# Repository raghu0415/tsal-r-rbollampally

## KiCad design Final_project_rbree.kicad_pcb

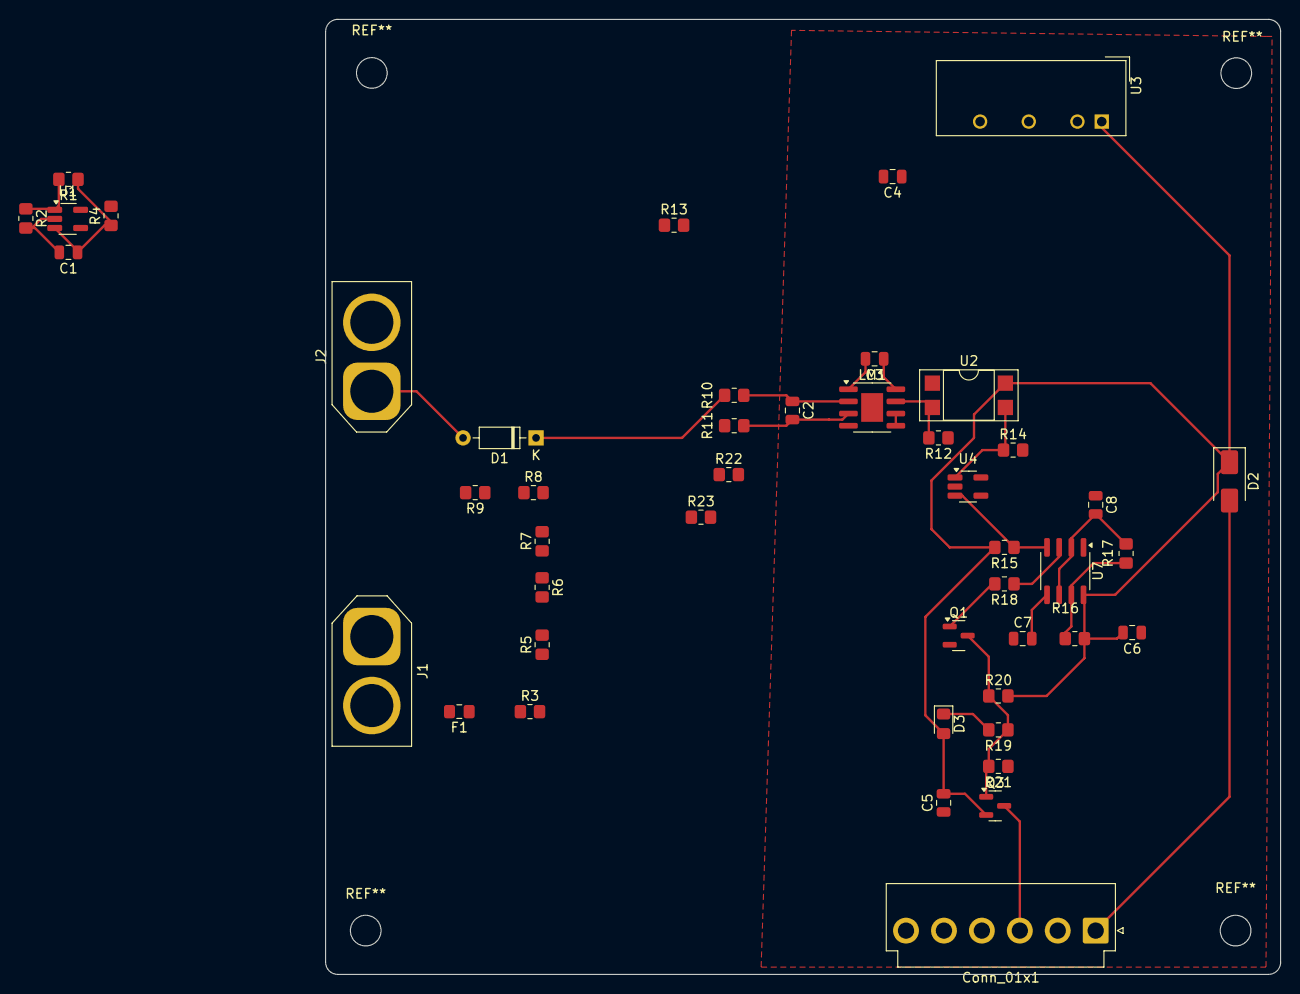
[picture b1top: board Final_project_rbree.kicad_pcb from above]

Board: 2 copper layers, 99.7 x 99.7 mm, 46 parts (0 on the bottom side), 29 nets.

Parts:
C1: 0.1uF; C_0805_2012Metric
C2: 10n; C_0805_2012Metric
C3, C6, C7: 100n; C_0805_2012Metric
C4: 1uF; C_0805_2012Metric
C5: 2.2uF; C_0805_2012Metric
C8: 1u; C_0805_2012Metric
Conn_01x1: Conn_01x06; JST_VH_B6P-VH_1x06_P3.96mm_Vertical
D1: 12V; D_DO-35_SOD27_P7.62mm_Horizontal
D2: D; D_SMA
D3: LED; LED_0805_2012Metric_Pad1.15x1.40mm_HandSolder
F1: Fuse; Fuse_0805_2012Metric_Pad1.15x1.40mm_HandSolder
J1, J2: Conn_01x02_Pin; AMASS_XT60-M_1x02_P7.20mm_Vertical
LM1: LM311; SOIC-8-1EP_3.9x4.9mm_P1.27mm_EP2.29x3mm
Q1: MMBT3904; SOT-23
Q3: AO3401A; SOT-23
R1: 2k; R_0805_2012Metric_Pad1.20x1.40mm_HandSolder
R2, R14: 10k; R_0805_2012Metric_Pad1.20x1.40mm_HandSolder
R3, R5, R6, R7: 249k; R_0805_2012Metric_Pad1.20x1.40mm_HandSolder
R4, R13: 2k2; R_0805_2012Metric_Pad1.20x1.40mm_HandSolder
R8: 25k; R_0805_2012Metric_Pad1.20x1.40mm_HandSolder
R9, R18, R19, R20, R22, R23: 1k; R_0805_2012Metric_Pad1.20x1.40mm_HandSolder
R10, R11: 100; R_0805_2012Metric_Pad1.20x1.40mm_HandSolder
R12: 1M; R_0805_2012Metric_Pad1.20x1.40mm_HandSolder
R15, R16: 22k; R_0805_2012Metric_Pad1.20x1.40mm_HandSolder
R17: 220k; R_0805_2012Metric_Pad1.20x1.40mm_HandSolder
R21: 100k; R_0805_2012Metric_Pad1.20x1.40mm_HandSolder
U1: TL431; SOT-23-5_HandSoldering
U2: LTV-817; DIP-4_W7.62mm_SMDSocket_SmallPads
U3: B1212; Converter_DCDC_TRACO_TBA2-xxxx_Single_THT
U4: 2N7002; SOT-23-5_HandSoldering
U7: NE555; SOIC-8_3.9x4.9mm_P1.27mm

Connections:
+12V: C3.1, C4.2, LM1.8 (V+), R4.2, R13.1, U3.6 (+Vout)
/RED+: Conn_01x1.3, Q3.3 (D)
/Vin: D1.1 (K), R7.2, R8.2, R10.2, R12.1
/Vref: R11.2, R22.1, R23.2
GLV+: Conn_01x1.1, D2.2 (A)
GLV-: C5.1, C6.1, C7.1, C8.1, Conn_01x1.4, Conn_01x1.5, Conn_01x1.6, Q1.2 (E), R14.2, R21.1, U3.2 (-Vin), U4.2 (S), U7.1 (GND)
GND: C1.2, C3.2, C4.1, D1.2 (A), J2.1, LM1.1 (GND), LM1.4 (V-), R2.2, R9.2, R22.2, U1.2 (A), U3.4 (-Vout)
unnamed: D3.1 (K), R19.2
unnamed: F1.1, R3.1
unnamed: F1.2, J1.2
unnamed: C2.1, LM1.2 (+), R10.1
unnamed: C2.2, LM1.3 (-), R11.1
unnamed: LM1.5 (BAL), LM1.6 (STRB)
unnamed: LM1.7, R12.2, U2.2
unnamed: Q1.1 (B), R18.2
unnamed: Q1.3 (C), Q3.1 (G), R19.1, R20.1, R21.2
unnamed: R3.2, R5.1
unnamed: R5.2, R6.2
unnamed: R6.1, R7.1
unnamed: R8.1, R9.1
unnamed: R13.2, U2.1
unnamed: R1.2, R2.1, U1.1 (REF)
unnamed: R15.1, U4.3 (D), U7.4 (R)
unnamed: R14.1, U2.3, U4.1 (G)
unnamed: C7.2, U7.5 (CV)
unnamed: R16.1, R17.2, U7.7 (DIS)
unnamed: R18.1, U7.3 (Q)
unnamed: C8.2, R17.1, U7.2 (TR), U7.6 (THR)
VCC: C5.2, C6.2, D2.1 (K), D3.2 (A), Q3.2 (S), R15.2, R16.2, R20.2, U2.4, U3.1 (+Vin), U7.8 (VCC)

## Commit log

2025-01-25 Commit - 2
    nothing
2025-01-31 commit - final
